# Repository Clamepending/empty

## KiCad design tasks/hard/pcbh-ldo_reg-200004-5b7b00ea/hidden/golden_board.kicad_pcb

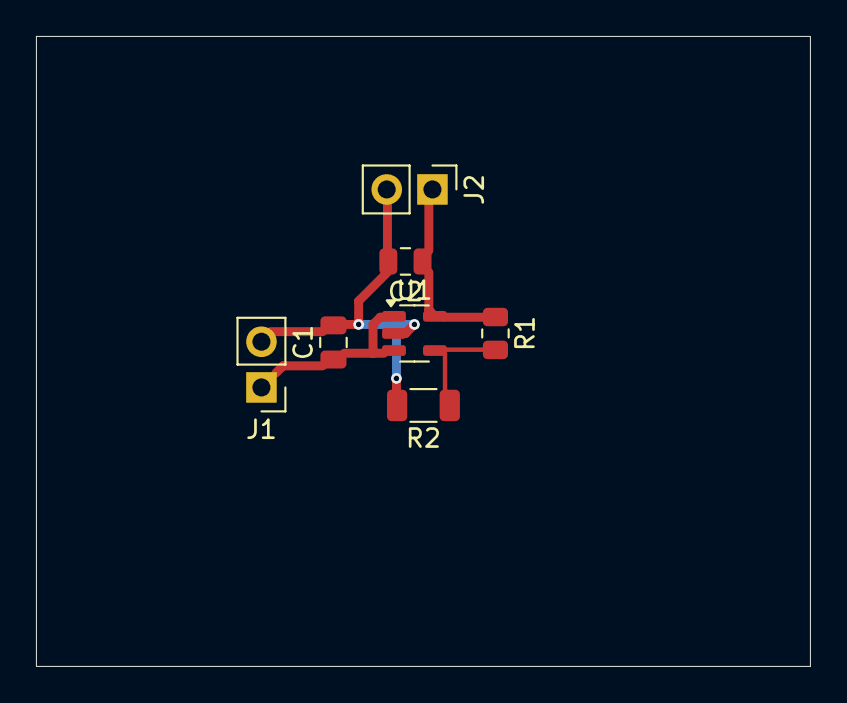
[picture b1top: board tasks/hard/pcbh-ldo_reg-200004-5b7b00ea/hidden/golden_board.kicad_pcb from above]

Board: 2 copper layers, 43.0 x 35.0 mm, 7 parts (0 on the bottom side), 4 nets.

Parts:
C1: 10u; C_0805_2012Metric
C2: 1u; C_0805_2012Metric
J1, J2: PinHeader_1x02_P2.54mm_Vertical
R1: 48.7k; R_0805_2012Metric
R2: 19.6k; R_1206_3216Metric
U1: SOT-23-5

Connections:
+2V8: C2.1, J2.1, R1.1, U1.5
FB: R1.2, R2.1, U1.4
GND: C1.2, C2.2, J1.2, J2.2, R2.2, U1.2
VIN: C1.1, J1.1, U1.1, U1.3

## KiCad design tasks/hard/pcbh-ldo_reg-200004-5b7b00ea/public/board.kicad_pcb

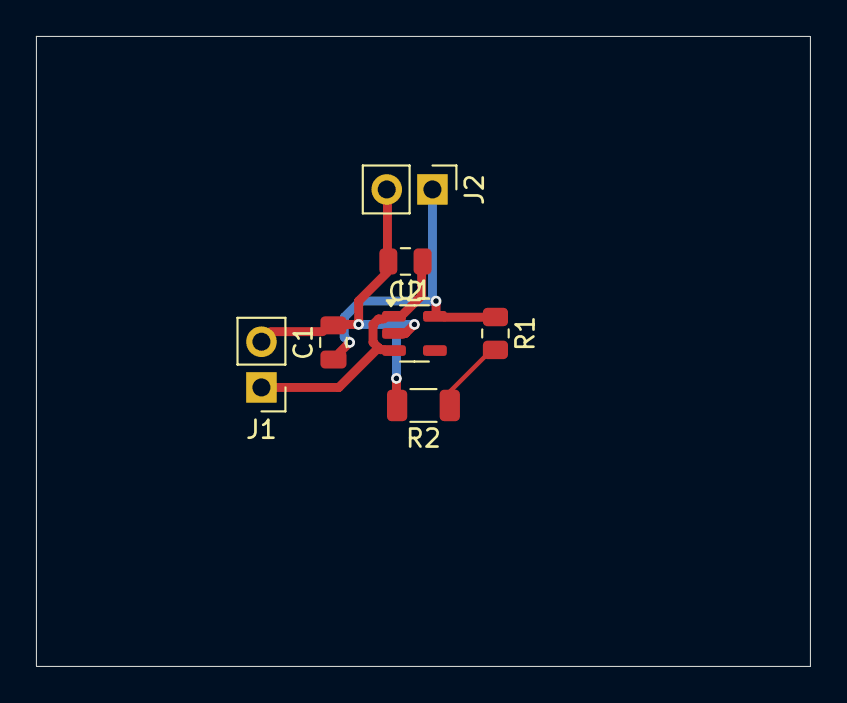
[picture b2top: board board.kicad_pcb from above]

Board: 2 copper layers, 43.0 x 35.0 mm, 7 parts (0 on the bottom side), 4 nets.

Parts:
C1: 10u; C_0805_2012Metric
C2: 1u; C_0805_2012Metric
J1, J2: PinHeader_1x02_P2.54mm_Vertical
R1: 36.5k; R_0805_2012Metric
R2: 43k; R_1206_3216Metric
U1: SOT-23-5

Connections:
+2V8: C1.1, J2.1, R1.1, U1.5
FB: R1.2, R2.1
GND: C1.2, C2.2, J1.2, J2.2, R2.2, U1.2
VIN: C2.1, J1.1, U1.1, U1.3

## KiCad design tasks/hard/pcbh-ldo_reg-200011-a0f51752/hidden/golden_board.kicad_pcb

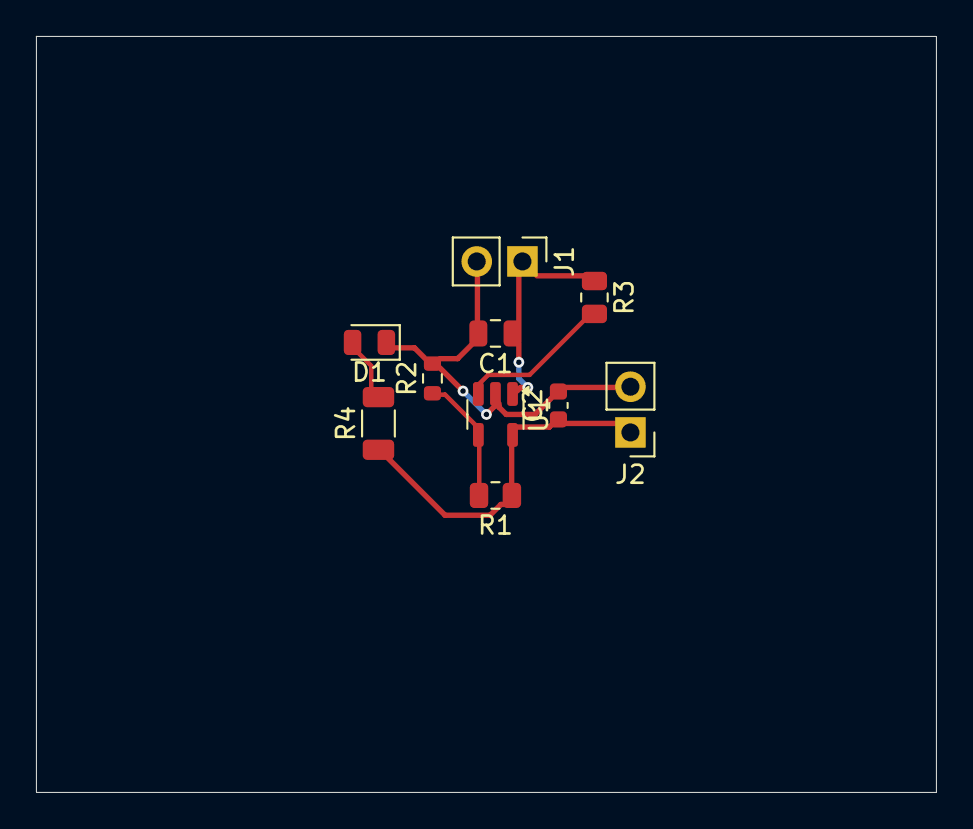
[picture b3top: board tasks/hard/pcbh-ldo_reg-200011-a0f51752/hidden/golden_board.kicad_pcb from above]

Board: 2 copper layers, 50.0 x 42.0 mm, 10 parts (0 on the bottom side), 6 nets.

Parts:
C1: 4.7u; C_0805_2012Metric
C2: 4.7u; C_0603_1608Metric
D1: LED_0805_2012Metric
J1, J2: PinHeader_1x02_P2.54mm_Vertical
R1: 105k; R_0805_2012Metric
R2: 33.2k; R_0603_1608Metric
R3: 100k; R_0805_2012Metric
R4: 680; R_1206_3216Metric
U1: SOT-23-5

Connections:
+3V3: C2.1, J2.1, R1.1, R4.1, U1.5
EN: R3.2, U1.3
FB: R1.2, R2.1, U1.4
GND: C1.2, C2.2, D1.1, J1.2, J2.2, R2.2, U1.2
LED: D1.2, R4.2
VIN: C1.1, J1.1, R3.1, U1.1
